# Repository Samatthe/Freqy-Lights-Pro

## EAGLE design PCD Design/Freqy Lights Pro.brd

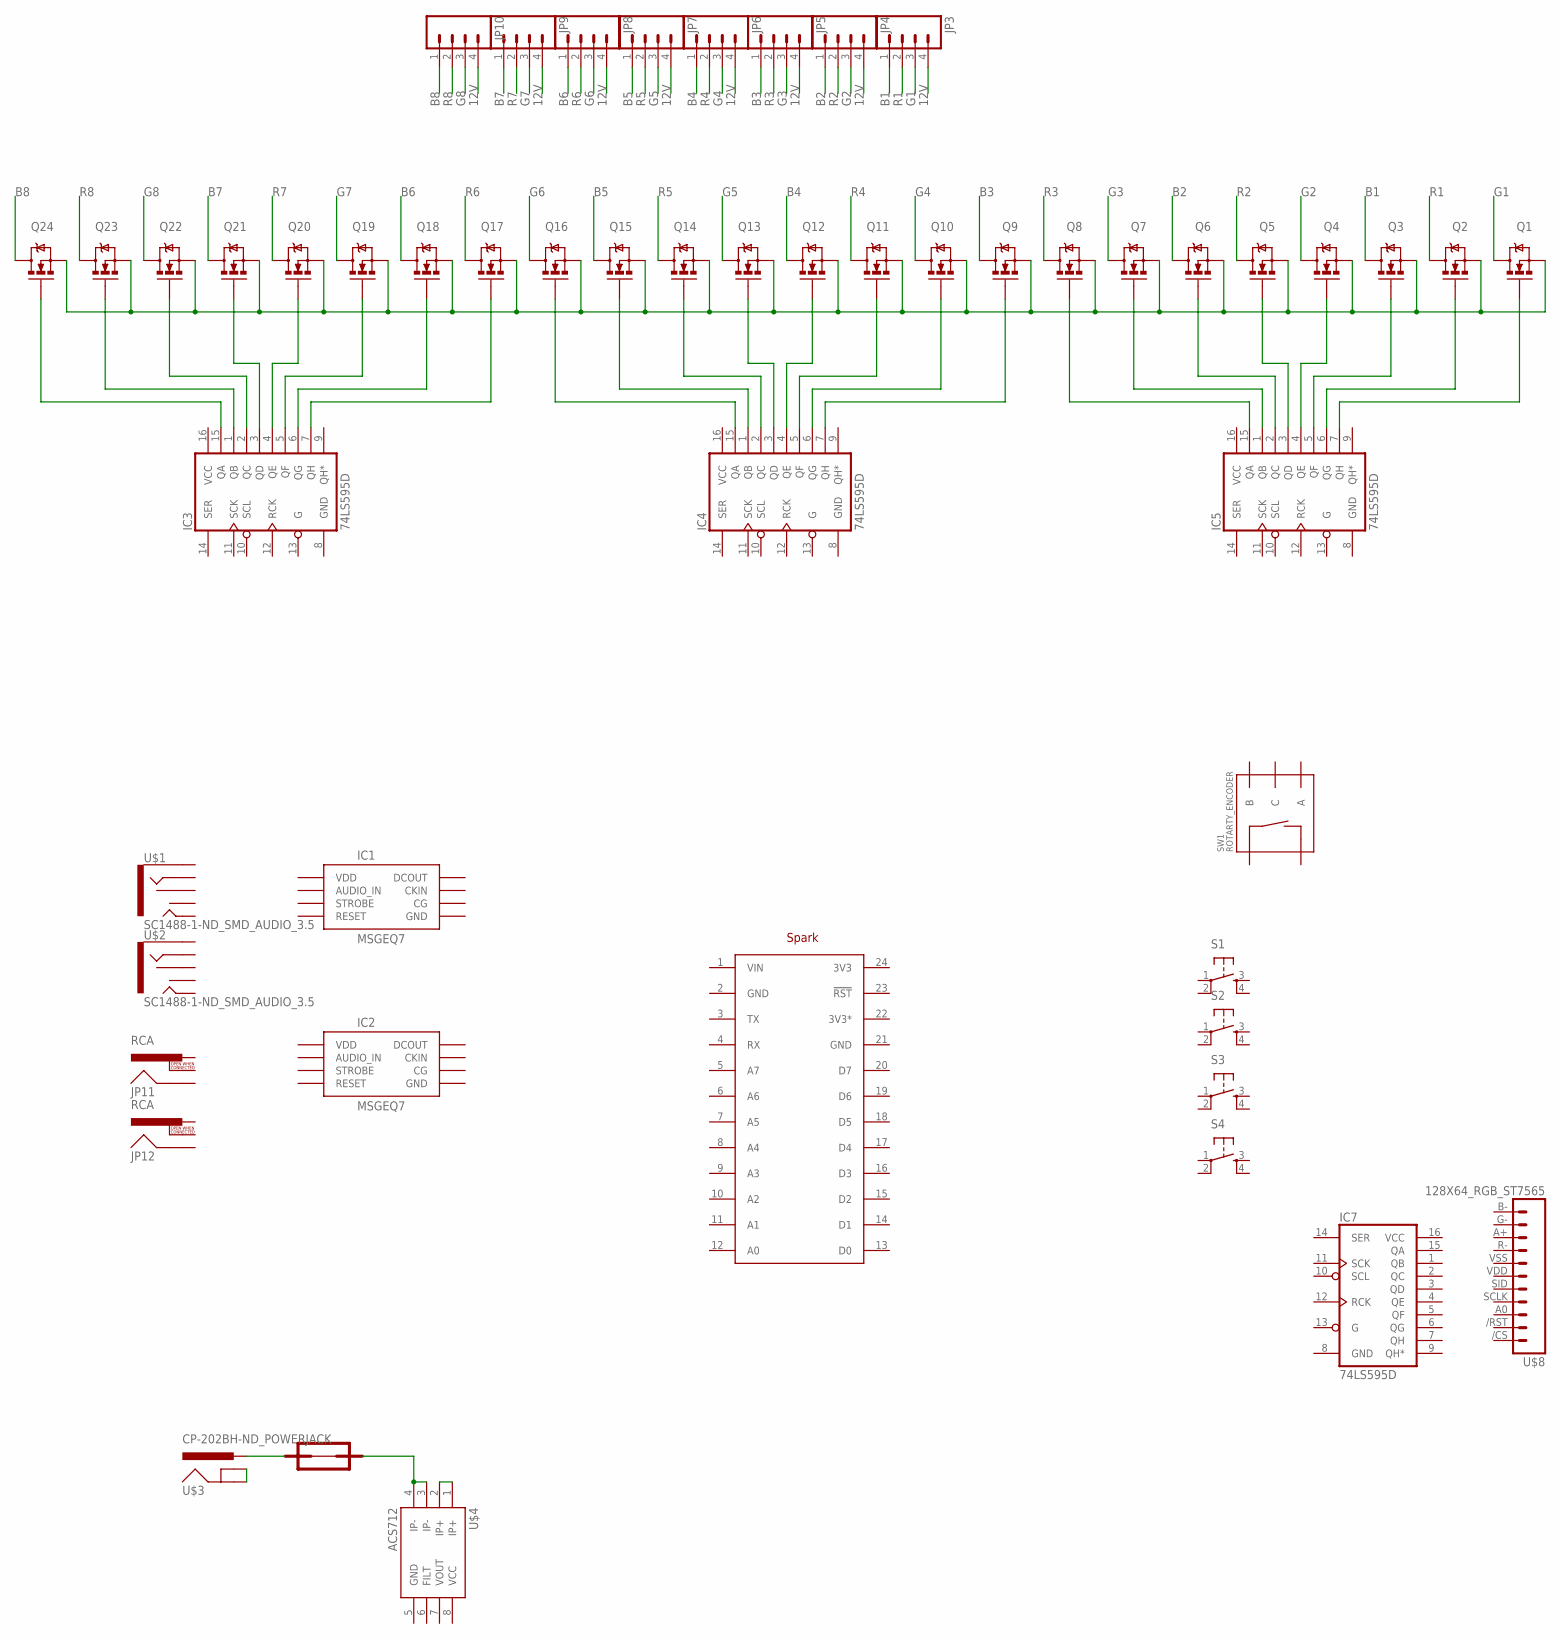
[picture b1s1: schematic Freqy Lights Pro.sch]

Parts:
IC1, IC2: MSGEQ7SOIC; SOIC8
IC3, IC4, IC5, IC7: 74LS595D; SO16
JP3, JP4, JP5, JP6, JP7, JP8, JP9, JP10: M04SCREW; SCREWTERMINAL-3.5MM-4
JP11, JP12: RCA
Q1, Q2, Q3, Q4, Q5, Q6, Q7, Q8, Q9, Q10, Q11, Q12, Q13, Q14, Q15, Q16, Q17, Q18, Q19, Q20, Q21, Q22, Q23, Q24: MOSFET-NCHANNELBSS123LT1G; SOT23
S1, S2, S3, S4: TAC_SWITCHPTH; TACTILE-PTH
SW1: ROTARTY_ENCODER; ROTARY_ENC_PLAIN
U$1, U$2: SC1488-1-ND_SMD_AUDIO_3.5; 3.5MM_SMD_AUDIO_SC1488-1-ND
U$3: CP-202BH-ND_POWERJACK; POWER_JACK_CP-202BH-ND
U$4: ACS712; SO08
U$5: SSQ12
U$8: 128X64_RGB_ST7565; ST7565_128X64_RGB
U$9: SPARK_LOGO_WITH_PLANE; SPARK_LOGO_PLUS_PLANE
U$10: SPARK_CORECORE; SPARK_CORE

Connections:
3V3: U$10.24 (3V3)
3V3*: U$10.22 (3V3*)
12V: JP3.4, JP4.4, JP5.4, JP6.4, JP7.4, JP8.4, JP9.4, JP10.4
B1: JP3.1, Q3.3 (D)
B2: JP4.1, Q6.3 (D)
B3: JP5.1, Q9.3 (D)
B4: JP6.1, Q12.3 (D)
B5: JP7.1, Q15.3 (D)
B6: JP8.1, Q18.3 (D)
B7: JP9.1, Q21.3 (D)
B8: JP10.1, Q24.3 (D)
G1: JP3.3, Q1.3 (D)
G2: JP4.3, Q4.3 (D)
G3: JP5.3, Q7.3 (D)
G4: JP6.3, Q10.3 (D)
G5: JP7.3, Q13.3 (D)
G6: JP8.3, Q16.3 (D)
G7: JP9.3, Q19.3 (D)
G8: JP10.3, Q22.3 (D)
GND: IC3.8 (GND), IC4.8 (GND), IC5.8 (GND), IC7.8 (GND), U$10.2 (GND), U$10.21 (GND)
unnamed: Q1.2 (S), Q2.2 (S), Q3.2 (S), Q4.2 (S), Q5.2 (S), Q6.2 (S), Q7.2 (S), Q8.2 (S), Q9.2 (S), Q10.2 (S), Q11.2 (S), Q12.2 (S), Q13.2 (S), Q14.2 (S), Q15.2 (S), Q16.2 (S), Q17.2 (S), Q18.2 (S), Q19.2 (S), Q20.2 (S), Q21.2 (S), Q22.2 (S), Q23.2 (S), Q24.2 (S)
unnamed: U$3.PWR, U$5.P$1
unnamed: U$3.GND, U$3.GNDBRK (GNDBREAK)
unnamed: U$4.3 (IP-), U$4.4 (IP-), U$5.P$2
unnamed: IC3.15 (QA), Q24.1 (G)
unnamed: IC3.1 (QB), Q23.1 (G)
unnamed: IC3.2 (QC), Q22.1 (G)
unnamed: IC3.3 (QD), Q21.1 (G)
unnamed: IC3.4 (QE), Q20.1 (G)
unnamed: IC3.5 (QF), Q19.1 (G)
unnamed: IC3.6 (QG), Q18.1 (G)
unnamed: IC3.7 (QH), Q17.1 (G)
unnamed: IC4.3 (QD), Q13.1 (G)
unnamed: IC4.4 (QE), Q12.1 (G)
unnamed: IC5.3 (QD), Q5.1 (G)
unnamed: IC5.4 (QE), Q4.1 (G)
unnamed: IC4.15 (QA), Q16.1 (G)
unnamed: IC4.1 (QB), Q15.1 (G)
unnamed: IC4.2 (QC), Q14.1 (G)
unnamed: IC4.5 (QF), Q11.1 (G)
unnamed: IC4.6 (QG), Q10.1 (G)
unnamed: IC4.7 (QH), Q9.1 (G)
unnamed: IC5.15 (QA), Q8.1 (G)
unnamed: IC5.1 (QB), Q7.1 (G)
unnamed: IC5.2 (QC), Q6.1 (G)
unnamed: IC5.7 (QH), Q1.1 (G)
unnamed: IC5.6 (QG), Q2.1 (G)
unnamed: IC5.5 (QF), Q3.1 (G)
unnamed: U$4.1 (IP+), U$4.2 (IP+)
R1: JP3.2, Q2.3 (D)
R2: JP4.2, Q5.3 (D)
R3: JP5.2, Q8.3 (D)
R4: JP6.2, Q11.3 (D)
R5: JP7.2, Q14.3 (D)
R6: JP8.2, Q17.3 (D)
R7: JP9.2, Q20.3 (D)
R8: JP10.2, Q23.3 (D)
VCC: IC3.16 (VCC), IC4.16 (VCC), IC5.16 (VCC), IC7.16 (VCC)
VIN: U$10.1 (VIN)

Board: 2 copper layers, 53 parts (0 on the bottom side), 56 nets, no tracks yet.

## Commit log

2015-09-28 :octocat: Added .gitattributes & .gitignore files
2015-09-28 added Eagle files to repo

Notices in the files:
parts and their libraries:
SparkFun-Connectors: Licensing: CC v3.0 Share-Alike You are welcome to use this library for commercial purposes.
